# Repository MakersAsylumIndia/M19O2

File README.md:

# M19O2
DiY Oxygen Concentrator based on / inspired by the [OpenOx](https://github.com/hacklabkyiv/openox), [Marut](https://www.technido.com/marut), [RepRap](https://github.com/RepRapLtd/Oxygen-concentrator) and [Project Apollo](https://github.com/oxycon/ProjectApollo) platforms.

## About

Read about the project on [Hackaday](https://hackaday.com/2021/04/26/indian-makers-respond-to-the-covid-19-pandemic-by-producing-oxygen-concentrators/).
Also check out the project on the [hackaday.io](https://hackaday.io/project/181201-m19o2-oxygen-concentrator) project page.

The **M19O2** Oxygen Concentrator is "Open Source Hardware" as certified by the [OSHWA](https://certification.oshwa.org/in000029.html).
OSHWA UID for the M19O2 is **IN000029**

<a href="https://certification.oshwa.org/in000029.html">

## Contribute

You can contribute on the [Ketto fundraiser page](https://www.ketto.org/fundraiser/m19-oxygen-concentrators-make-in-india)

## Coordination lists

- [Notion workspace](https://www.notion.so/M-19-Collective-b44b9d8d7dd14d5d86d417facf0f4141) for the M19 collective.
- [M19O2 Master](https://docs.google.com/spreadsheets/d/1rJZ5P0rF2Or8yu0H8HEPz25RP8kTAXxbNVU87DqD-eM/edit#gid=0) sheet tracks the city-wise coordinators, tools, FAQs etc.
- [BOM M19O2](https://docs.google.com/spreadsheets/d/1gmmdXTP3EQk-4hCGVYj-FxzUMADlT8mw354VPmYt5A4/edit#gid=870920932) sheet lists the master Bill of Materials (BOM) along with city-wise BOM
- [Starting a community lab](https://docs.google.com/document/d/1oR9rhGmbcnoSBjzQCYwE9Anocvr0q5_VmuVkbnycx18/edit?usp=sharing) document and [Build List for Labs](https://docs.google.com/spreadsheets/d/1DynT9Mh8jcV9qHxwFuQxj1fcQQHj_v_ymwpoZD1L23g/edit?usp=sharing) sheet for lab onboarding information and coordination.

## Engineering

- [Labview testbench](engineering/software/M19-oxygen-concentrator-testbench) is a testbench executable developed by [Fracktal Works](https://github.com/FracktalWorks), useful for tuning the performance of your concentrator prototypes.
- [Computer-aided Design/Engineering](engineering/cad-cae) for design, version control and simulation data related to the M19O2 and its iterations. Committed to open-source and open-innovation.
- [Electronics](engineering/electronics) for all things electronics, including comprehensive design and development data of DIY [Oxygen Analyzers](engineering/electronics/oxygen_analysers) and other [subprojects](engineering/electronics/subprojects).

## How to use this repo

Open a terminal on your computer. Run

```bash
git clone https://github.com/MakersAsylumIndia/M19O2 && cd M19O2
git submodule update --init --recursive
```
The repository shall be available on your computer.
To periodically update the contents,

```bash
cd M19O2
git pull
git submodule update --init --recursive
```

## How to contribute to this repository

Fork this repository. You can find the command for this on the top-right of the webpage. This shall create a personal, updateable copy of this repository on your github account.

On your computer terminal, run

```bash
git clone https://github.com/<your-username>/M19O2 && cd M19O2
git submodule update --init --recursive
```
Add your contributions to this repository and save on github.

```bash
cd M19O2
git add .
git commit -m "<your-commit-message>"
git push origin
```

To contribute your work to the M19 Collective, open your repository in a browser and issue a pull request from your repository to the one at [Makers' Asylum](https://github.com/MakersAsylumIndia).

## License

Licenses

#### Hardware
CERN Open Hardware License Version 2 - Strongly Reciprocal ([CERN-OHL-S-2.0](https://spdx.org/licenses/CERN-OHL-S-2.0.html)).

#### Software
MIT open source [license](http://opensource.org/licenses/MIT).

#### Documentation:
<br />This work is licensed under a <a rel="license" href="http://creativecommons.org/licenses/by/4.0/">Creative Commons Attribution 4.0 International License</a>.

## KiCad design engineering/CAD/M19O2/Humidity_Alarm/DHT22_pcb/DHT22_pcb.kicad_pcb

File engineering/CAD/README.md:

This folder is dedicated to M19O2 CAD files and version-control.

*Starting/Kickoff contents*
M19O2 - 
 * FCstd file (FreeCAD v0.19) and STEP/STL export formats
 * FCstd files for sub-projects such as sieve compression jig, sieve assembly, O2 sensor housing, Humidity sensor housing etc.

Oxikit_v22 - (DEPRECATED and moved to ARCHIVE)
 * F3D file (Fusion 360), 
 * STEP file (converted from F3D),
 * STL file (converted from STEP. for light *3d viewing* only) 
 * FreeCAD document (converted from STEP file. No feature model)

 * All individual OxiKit parts (exported from Fusion) as STEP files.

*TODO*
 * Convert F3D feature model appropriately to FreeCAD. --> Make freecad assembly with step files.
 * Set up framework for newer local design iterations and dimensional variants.
 * Integrate local subassembles/component information and product BoM management

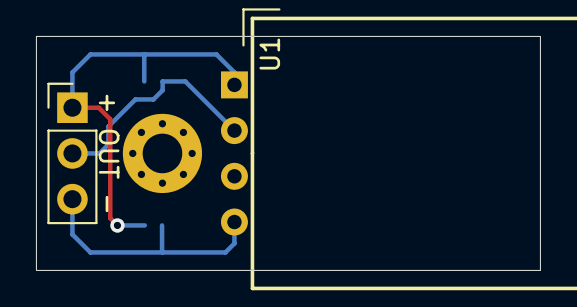
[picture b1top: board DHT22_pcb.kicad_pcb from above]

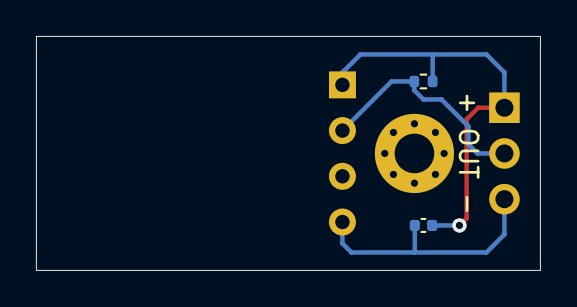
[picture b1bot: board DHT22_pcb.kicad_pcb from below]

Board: 2 copper layers, 28.0 x 13.0 mm, 5 parts (2 on the bottom side), 3 nets.

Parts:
C1: 100nF; C_0402_1005Metric
H1: MountingHole; MountingHole_2.2mm_M2_Pad_Via
J1: Output; PinHeader_1x03_P2.54mm_Vertical
R1: 4k7; R_0402_1005Metric
U1: DHT22; Aosong_DHT22_horiz

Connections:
/GND: C1.2, J1.3, U1.4
/OUT: J1.2, R1.2, U1.2
/VCC: C1.1, J1.1, R1.1, U1.1

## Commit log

2021-04-28 initial commit for M19 OxiKit project
2021-04-28 Update README.md
    added render image
2021-04-29 electronics sub-project
2021-04-29 DOC: project coordination links
2021-04-29 renamed images
2021-04-30 Added README and starting CAD content
2021-04-30 [FEATURE] Submodules for cad and sd - argo-1 repos at the moment
2021-04-30 Updated submodules
2021-04-30 Oxikit DIY oxygen analyser documents added.
2021-04-30 updated SD
2021-04-30 basic update
2021-04-30 added empty CAE submodule
2021-04-30 CAE submodule added and set-up
2021-04-30 simple fix
2021-04-30 Added submodule for electronics
2021-04-30 Added instructables.com page (.html)
2021-04-30 updated electronics submodule
2021-04-30 OxiKit docs
2021-05-01 Added valve step files to cad submodule
2021-05-01 Completed all individual parts' step-file conversion
2021-05-01 Updated CAD submodule
2021-05-01 Started FreeCAD Assembly of OxiKit v22
2021-05-01 Made frame FreeCAD assembly. Unconstrained. Added to parent assembly
2021-05-01 Updated CAD assembly of v22
2021-05-02 Updated tubing on freecad assembly
2021-05-02 Updated assembly - top solenoid fitting - reset tubes
2021-05-02 Updated tanks in assembly
2021-05-02 Updated assembly (unconstrained). Only tubing left.
2021-05-03 Merged and updated electronics folder.
2021-05-06 [FEATURE] Merged MeshAssembly PR
2021-05-07 ENH: add a period
2021-05-07 DOC: minor phrase update
2021-05-19 Simplified structure. Removed submodules, for now.
2021-05-19 [FEATURE] Restructuring.
2021-05-19 Wiki markdown copies added to /docs. THESE FILES ARE NOT LINKED TO THE WIKI TAB DIRECTLY
2021-05-21 Simulation research and IISc docs
2021-05-21 tata doc
2021-05-21 Added lab onboarding to README.md
2021-05-21 nafion tubes paper
2021-05-22 [FEATURE]Added Labview testbench. Updated README.md
2021-05-22 [FIX] Readme typo
2021-05-22 [ENHANCEMENT] Updated README.md
2021-05-23 [FEATURE] DIY Oxygen Analyzer
2021-05-23 [FIX] rearrange
2021-05-24 [FIX] Readme link
2021-05-24 [FEATURE] Add Karan's project. Minor restructuring
2021-05-25 [ENHANCEMENT] expanded deployment folder structure
2021-06-01 Brainboard by @shridattdudhat added
2021-06-01 Fracktal firmware
2021-06-10 [FEATURE] Add Fracktal Works OC data
2021-06-10 added humidity alarm
2021-06-10 Update README.md
    Edited readme
2021-06-10 added O2 sensor adapter
2021-06-11 Updated Readme - notion
2021-06-11 update readme - notion
2021-06-11 [fix] prune stale submodule
2021-06-12 added LiX zeolite timing code WIP
2021-06-14 added Sieve aluminum extrusion assembly in CAD folder WIP
2021-06-18 sieve bed exploded view, patent and extrustion standard
2021-06-18 sieve bed exploded view, patent and extrustion standard (#21)
2021-06-27 Update README.md
    minor updates
2021-06-27 Sieve Assembly, Sieve Compression Jig, Humidity Sensor housings etc
2021-06-27 added logos
2021-06-29 folder restructuring and added M19O2 wiring in Electronics
2021-06-30 started M19O2_v4 CAD assy
2021-07-04 finished M19O2_v4 CAD assy
2021-07-05 M19O2 pneumatic circuit added
2021-07-08 [FEATURE] WHO guidelines
2021-07-09 M19O2 CAD updates
2021-07-16 M19O2 pneumatic wiring update
2021-07-17 M19O2 added O2 sensor measurement code and main code
2021-07-26 M19O2 Datasheet & Instruction Manual update
2021-07-30 M19O2 Oxygen sensor mount
    M19O2 Oxygen sensor mount
2021-08-06 M19O2 extracted assembly images from CAD
2021-08-06 M19O2 added better renders for readme.md
2021-08-13 M19O2 several incremental updates
2021-08-13 M19O2 assembly manual added
2021-08-13 Update README.md
    added hackaday.io project page link
2021-08-19 M19O2 added moisture separator and auto drain STEP files
2021-08-24 added OSHWA certification logo
2021-09-04 big push - added Hour Counter, and modified all renders and drawings
2021-09-17 some updates
2021-09-17 documents update
2021-10-21 documentation updates
2022-11-21 added hi-res 3D CAD renders

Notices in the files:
README.md:
Open Source Licenses Facts
